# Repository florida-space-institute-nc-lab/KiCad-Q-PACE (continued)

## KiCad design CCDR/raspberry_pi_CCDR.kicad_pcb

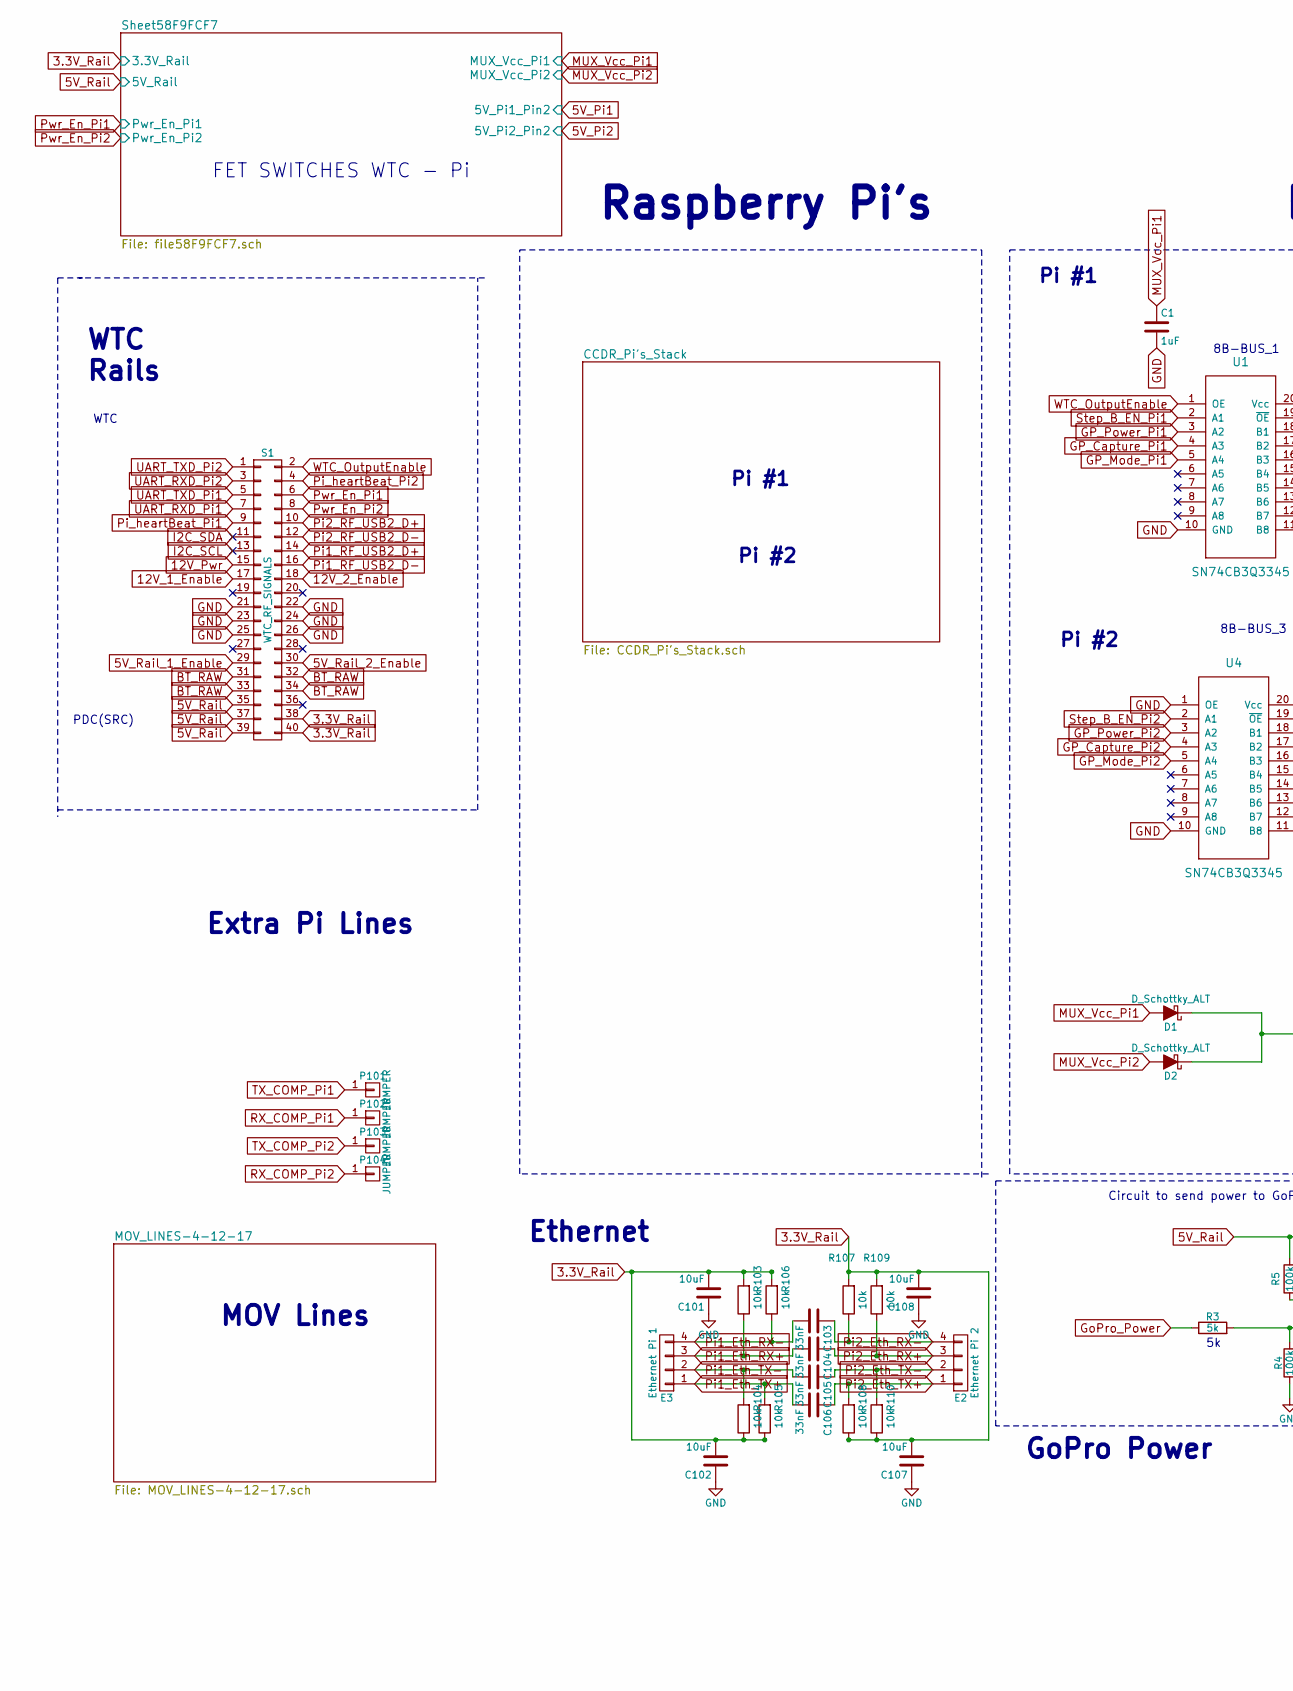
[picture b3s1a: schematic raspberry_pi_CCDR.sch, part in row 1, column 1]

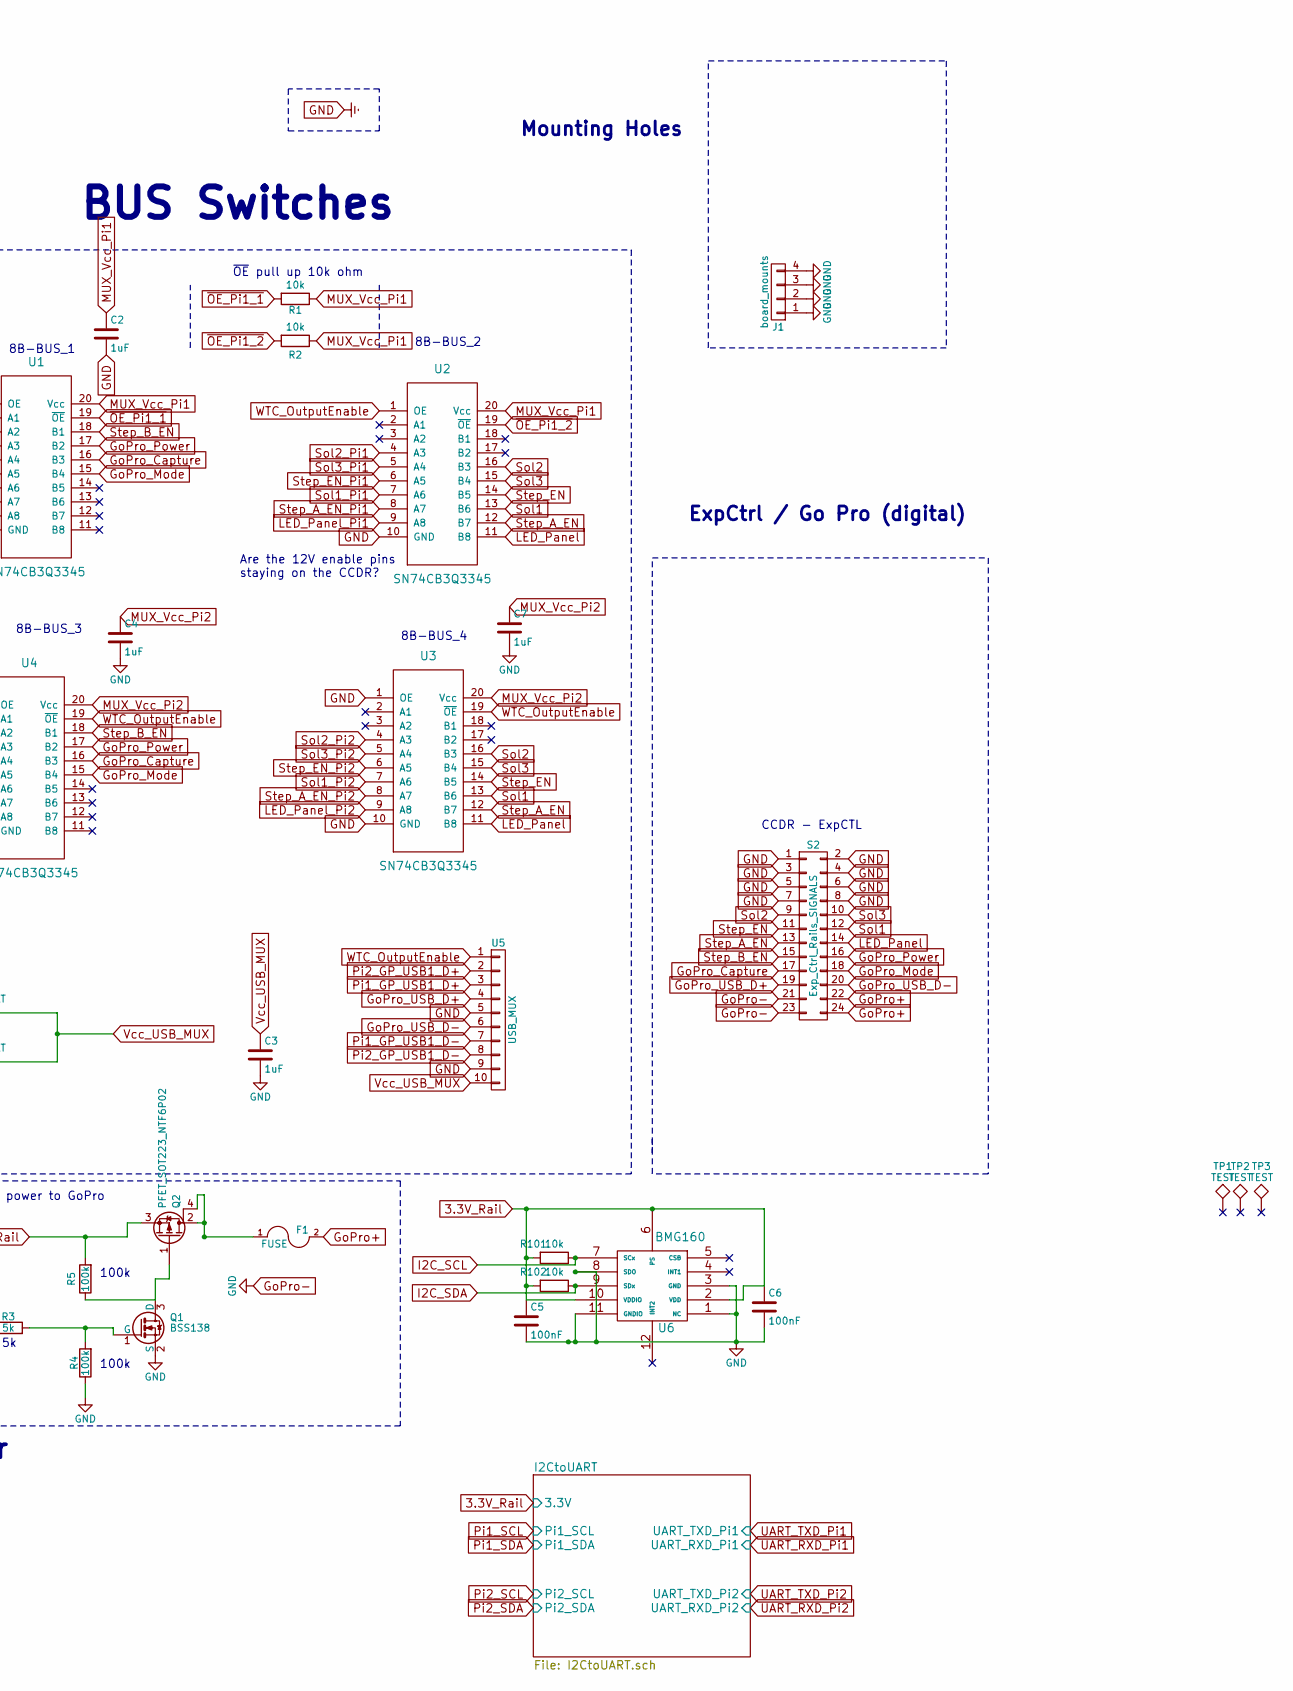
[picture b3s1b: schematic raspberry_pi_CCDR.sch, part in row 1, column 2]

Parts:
C1, C2, C3, C4, C7: 1uF; C_0805_HandSoldering
C5, C6: 100nF; C_0805
C101, C102, C107, C108: 10uF; C_0805
C103, C104, C105, C106: 33nF; C_0805
D1, D2: D_Schottky_ALT; SOD-128
E2: Ethernet Pi 2; 01x04-conn-sq
E3: Ethernet Pi 1; 01x04-conn-sq
F1: FUSE; 2-SMD_Fuse
J1: board_mounts; boardMount_0125in060
P101, P102, P103, P104: JUMPER; PINTST
Q1: BSS138; N-Fet_BSS138_SOT-23
Q2: PFET_SOT223_NTF6P02; SOT-223_GDS
R1, R2, R101, R102, R103, R104, R105, R106, R107, R108, R109, R110: 10k; R_0805
R3: 5k; R_0805
R4, R5: 100k; R_0805
S1: WTC_RF_SIGNALS; Samtec_SSQ-120-03-G-D_QPACE_40-Pin_r1
S2: Exp_Ctrl_Rails_SIGNALS; Samtec_SSQ-112-03-G-D
TP1, TP2, TP3: TEST; Fiducial_0.5mm_Dia_1mm_Outer_FB
U1, U2, U3, U4: SN74CB3Q3345; bus_switch_sn74cb3q3345_rev2
U5: USB_MUX; USB_MUX-TS3USB30E-DGS
U6: BMG160; LGA-12_2x2mm_Pitch0.5mm

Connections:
3.3V_Rail: C5.1, C6.1, C101.2, C102.2, C107.2, C108.2, R101.2, R102.2, R103.2, R104.1, R105.1, R106.2, R107.2, R108.1, R109.2, R110.1, S1.38, S1.40, U6.2 (VDD), U6.6 (PS), U6.10 (VDDIO); also elsewhere on the board
5V_Rail: Q2.3 (S), R5.2, S1.35, S1.37, S1.39; also elsewhere on the board
5V_Rail_1_Enable: S1.29
5V_Rail_2_Enable: S1.30
12V_1_Enable: S1.17
12V_2_Enable: S1.18
12V_Pwr: S1.15
BT_RAW: S1.31, S1.32, S1.33, S1.34
GND: C1.2, C2.2, C3.2, C4.2, C5.2, C6.2, C7.2, C101.1, C102.1, C107.1, C108.1, J1.1, J1.2, J1.3, J1.4, Q1.2 (S), R4.1, S1.21, S1.22, S1.23, S1.24, S1.25, S1.26, S2.1, S2.2, S2.3, S2.4, S2.5, S2.6, S2.7, S2.8, S2.21, S2.23, U1.10 (GND), U2.10 (GND), U3.1 (OE), U3.10 (GND), U4.1 (OE), U4.10 (GND), U5.5, U5.9, U6.1 (NC), U6.3 (GND), U6.8 (SDO), U6.11 (GNDIO); also elsewhere on the board
GP_Capture_Pi1: U1.4 (A3); also elsewhere on the board
GP_Capture_Pi2: U4.4 (A3); also elsewhere on the board
GP_Mode_Pi1: U1.5 (A4); also elsewhere on the board
GP_Mode_Pi2: U4.5 (A4); also elsewhere on the board
GP_Power_Pi1: U1.3 (A2); also elsewhere on the board
GP_Power_Pi2: U4.3 (A2); also elsewhere on the board
GoPro+: F1.2, S2.22, S2.24
GoPro_Capture: S2.17, U1.16 (B3), U4.16 (B3)
GoPro_Mode: S2.18, U1.15 (B4), U4.15 (B4)
GoPro_Power: R3.1, S2.16, U1.17 (B2), U4.17 (B2)
GoPro_USB_D+: S2.19, U5.4
GoPro_USB_D-: S2.20, U5.6
I2C_SCL: R101.1, S1.13, U6.7 (SCx)
I2C_SDA: R102.1, S1.11, U6.9 (SDx)
LED_Panel: S2.14, U2.11 (B8), U3.11 (B8)
LED_Panel_Pi1: U2.9 (A8); also elsewhere on the board
LED_Panel_Pi2: U3.9 (A8); also elsewhere on the board
MUX_Vcc_Pi1: C1.1, C2.1, D1.2 (A), R1.1, R2.1, U1.20 (Vcc), U2.20 (Vcc); also elsewhere on the board
MUX_Vcc_Pi2: C4.1, C7.1, D2.2 (A), U3.20 (Vcc), U4.20 (Vcc); also elsewhere on the board
unnamed: F1.1, Q2.2 (D), Q2.4 (D)
unnamed: Q1.1 (G), R3.2, R4.2
unnamed: Q1.3 (D), Q2.1 (G), R5.1
Pi1_Eth_RX+: C104.2, E3.3, R103.1
Pi1_Eth_RX-: C103.2, E3.4, R106.1
Pi1_Eth_TX+: C106.2, E3.1, R105.2
Pi1_Eth_TX-: C105.2, E3.2, R104.2
Pi1_GP_USB1_D+: U5.3; also elsewhere on the board
Pi1_GP_USB1_D-: U5.7; also elsewhere on the board
Pi1_RF_USB2_D+: S1.14; also elsewhere on the board
Pi1_RF_USB2_D-: S1.16; also elsewhere on the board
Pi2_Eth_RX+: C104.1, E2.3, R109.1
Pi2_Eth_RX-: C103.1, E2.4, R107.1
Pi2_Eth_TX+: C106.1, E2.1, R108.2
Pi2_Eth_TX-: C105.1, E2.2, R110.2
Pi2_GP_USB1_D+: U5.2; also elsewhere on the board
Pi2_GP_USB1_D-: U5.8; also elsewhere on the board
Pi2_RF_USB2_D+: S1.10; also elsewhere on the board
Pi2_RF_USB2_D-: S1.12; also elsewhere on the board
Pi_heartBeat_Pi1: S1.9; also elsewhere on the board
Pi_heartBeat_Pi2: S1.4; also elsewhere on the board
Pwr_En_Pi1: S1.6; also elsewhere on the board
Pwr_En_Pi2: S1.8; also elsewhere on the board
RX_COMP_Pi1: P102.1; also elsewhere on the board
RX_COMP_Pi2: P104.1; also elsewhere on the board
Sol1: S2.12, U2.13 (B6), U3.13 (B6)
Sol1_Pi1: U2.7 (A6); also elsewhere on the board
Sol1_Pi2: U3.7 (A6); also elsewhere on the board
Sol2: S2.9, U2.16 (B3), U3.16 (B3)
Sol2_Pi1: U2.4 (A3); also elsewhere on the board
Sol2_Pi2: U3.4 (A3); also elsewhere on the board
Sol3: S2.10, U2.15 (B4), U3.15 (B4)
Sol3_Pi1: U2.5 (A4); also elsewhere on the board
Sol3_Pi2: U3.5 (A4); also elsewhere on the board
Step_A_EN: S2.13, U2.12 (B7), U3.12 (B7)
Step_A_EN_Pi1: U2.8 (A7); also elsewhere on the board
Step_A_EN_Pi2: U3.8 (A7); also elsewhere on the board
Step_B_EN: S2.15, U1.18 (B1), U4.18 (B1)
Step_B_EN_Pi1: U1.2 (A1); also elsewhere on the board
Step_B_EN_Pi2: U4.2 (A1); also elsewhere on the board
Step_EN: S2.11, U2.14 (B5), U3.14 (B5)
Step_EN_Pi1: U2.6 (A5); also elsewhere on the board
Step_EN_Pi2: U3.6 (A5); also elsewhere on the board
TX_COMP_Pi1: P101.1; also elsewhere on the board
TX_COMP_Pi2: P103.1; also elsewhere on the board
UART_RXD_Pi1: S1.7; also elsewhere on the board
UART_RXD_Pi2: S1.3; also elsewhere on the board
UART_TXD_Pi1: S1.5; also elsewhere on the board
UART_TXD_Pi2: S1.1; also elsewhere on the board
Vcc_USB_MUX: C3.1, D1.1 (K), D2.1 (K), U5.10
WTC_OutputEnable: S1.2, U1.1 (OE), U2.1 (OE), U3.19 (~OE), U4.19 (~OE), U5.1
~OE_Pi1_1: R1.2, U1.19 (~OE)
~OE_Pi1_2: R2.2, U2.19 (~OE)

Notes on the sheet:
PDC(SRC)
8B-BUS_1
8B-BUS_2
8B-BUS_3
8B-BUS_4
CCDR - ExpCTL
Raspberry Pi's
BUS Switches
ExpCtrl / Go Pro (digital)
WTC Rails
GoPro Power
Mounting Holes
Pi #1
Pi #2
WTC
MOV Lines
~OE~ pull up 10k ohm
FET SWITCHES WTC - Pi
Circuit to send power to GoPro
Are the 12V enable pins staying on the CCDR?
100k
Extra Pi Lines
Ethernet

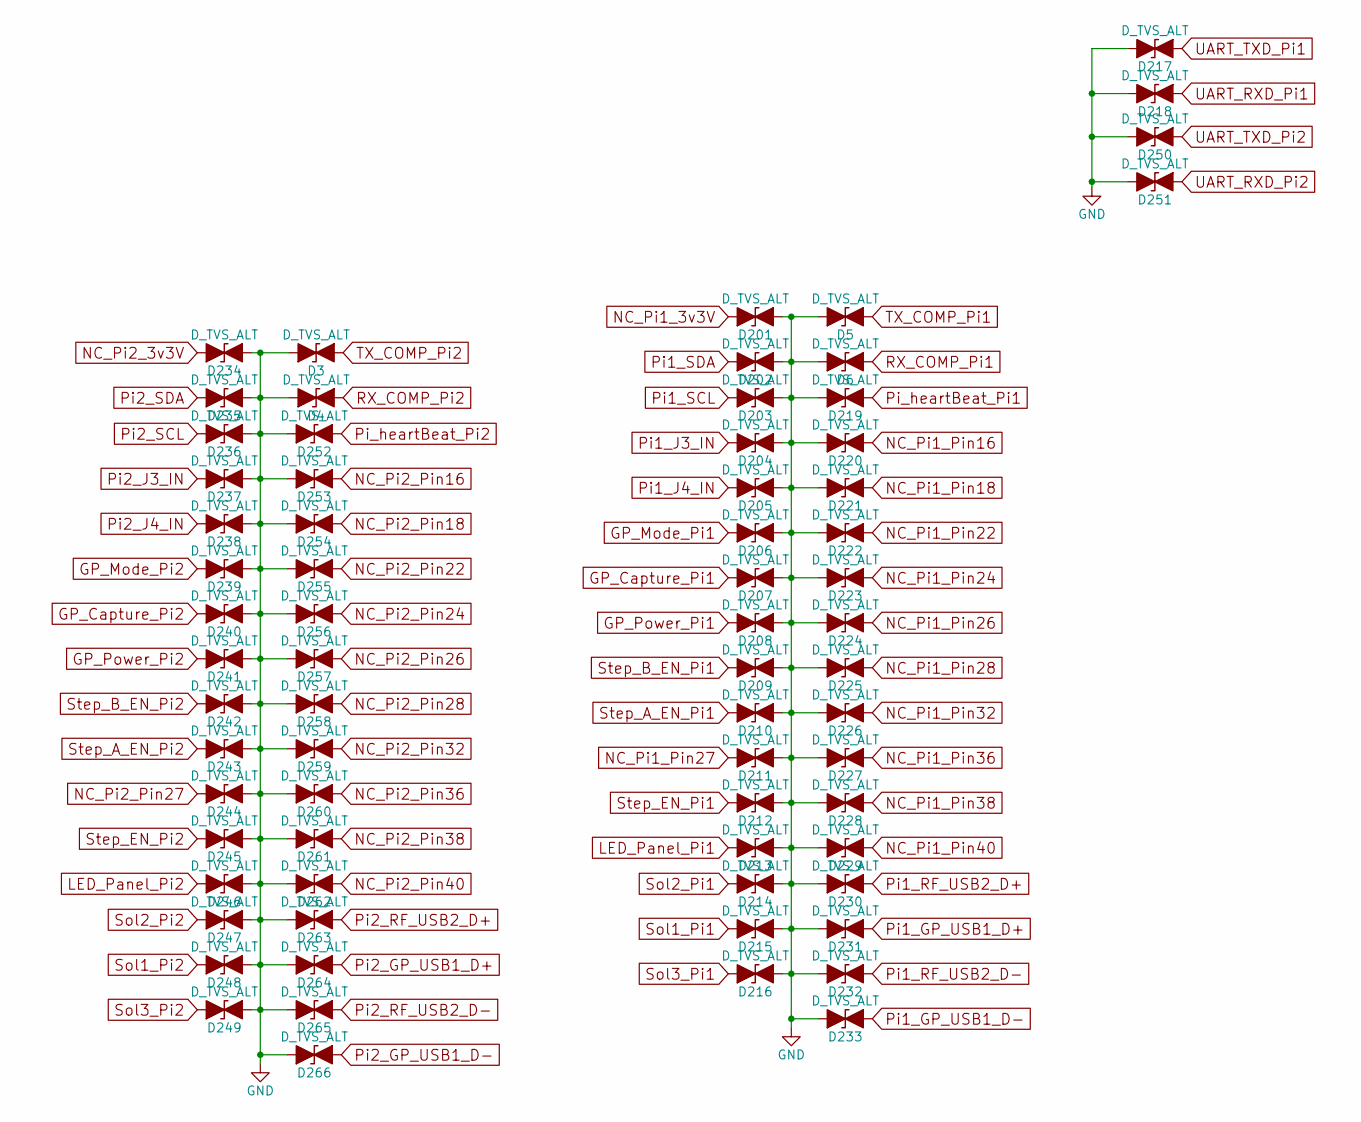
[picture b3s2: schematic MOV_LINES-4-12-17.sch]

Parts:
D3, D4, D5, D6, D201, D202, D203, D204, D205, D206, D207, D208, D209, D210, D211, D212, D213, D214, D215, D216, D217, D218, D219, D220, D221, D222, D223, D224, D225, D226, D227, D228, D229, D230, D231, D232, D233, D234, D235, D236, D237, D238, D239, D240, D241, D242, D243, D244, D245, D246, D247, D248, D249, D250, D251, D252, D253, D254, D255, D256, D257, D258, D259, D260, D261, D262, D263, D264, D265, D266: D_TVS_ALT; D_0805

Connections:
GND: D3.2 (A2), D4.2 (A2), D5.2 (A2), D6.2 (A2), D201.1 (A1), D202.1 (A1), D203.1 (A1), D204.1 (A1), D205.1 (A1), D206.1 (A1), D207.1 (A1), D208.1 (A1), D209.1 (A1), D210.1 (A1), D211.1 (A1), D212.1 (A1), D213.1 (A1), D214.1 (A1), D215.1 (A1), D216.1 (A1), D217.2 (A2), D218.2 (A2), D219.2 (A2), D220.2 (A2), D221.2 (A2), D222.2 (A2), D223.2 (A2), D224.2 (A2), D225.2 (A2), D226.2 (A2), D227.2 (A2), D228.2 (A2), D229.2 (A2), D230.2 (A2), D231.2 (A2), D232.2 (A2), D233.2 (A2), D234.1 (A1), D235.1 (A1), D236.1 (A1), D237.1 (A1), D238.1 (A1), D239.1 (A1), D240.1 (A1), D241.1 (A1), D242.1 (A1), D243.1 (A1), D244.1 (A1), D245.1 (A1), D246.1 (A1), D247.1 (A1), D248.1 (A1), D249.1 (A1), D250.2 (A2), D251.2 (A2), D252.2 (A2), D253.2 (A2), D254.2 (A2), D255.2 (A2), D256.2 (A2), D257.2 (A2), D258.2 (A2), D259.2 (A2), D260.2 (A2), D261.2 (A2), D262.2 (A2), D263.2 (A2), D264.2 (A2), D265.2 (A2), D266.2 (A2); also elsewhere on the board
GP_Capture_Pi1: D207.2 (A2); also elsewhere on the board
GP_Capture_Pi2: D240.2 (A2); also elsewhere on the board
GP_Mode_Pi1: D206.2 (A2); also elsewhere on the board
GP_Mode_Pi2: D239.2 (A2); also elsewhere on the board
GP_Power_Pi1: D208.2 (A2); also elsewhere on the board
GP_Power_Pi2: D241.2 (A2); also elsewhere on the board
LED_Panel_Pi1: D213.2 (A2); also elsewhere on the board
LED_Panel_Pi2: D246.2 (A2); also elsewhere on the board
NC_Pi1_3v3V: D201.2 (A2); also elsewhere on the board
NC_Pi1_Pin16: D220.1 (A1); also elsewhere on the board
NC_Pi1_Pin18: D221.1 (A1); also elsewhere on the board
NC_Pi1_Pin22: D222.1 (A1); also elsewhere on the board
NC_Pi1_Pin24: D223.1 (A1); also elsewhere on the board
NC_Pi1_Pin26: D224.1 (A1); also elsewhere on the board
NC_Pi1_Pin27: D211.2 (A2); also elsewhere on the board
NC_Pi1_Pin28: D225.1 (A1); also elsewhere on the board
NC_Pi1_Pin32: D226.1 (A1); also elsewhere on the board
NC_Pi1_Pin36: D227.1 (A1); also elsewhere on the board
NC_Pi1_Pin38: D228.1 (A1); also elsewhere on the board
NC_Pi1_Pin40: D229.1 (A1); also elsewhere on the board
NC_Pi2_3v3V: D234.2 (A2); also elsewhere on the board
NC_Pi2_Pin16: D253.1 (A1); also elsewhere on the board
NC_Pi2_Pin18: D254.1 (A1); also elsewhere on the board
NC_Pi2_Pin22: D255.1 (A1); also elsewhere on the board
NC_Pi2_Pin24: D256.1 (A1); also elsewhere on the board
NC_Pi2_Pin26: D257.1 (A1); also elsewhere on the board
NC_Pi2_Pin27: D244.2 (A2); also elsewhere on the board
NC_Pi2_Pin28: D258.1 (A1); also elsewhere on the board
NC_Pi2_Pin32: D259.1 (A1); also elsewhere on the board
NC_Pi2_Pin36: D260.1 (A1); also elsewhere on the board
NC_Pi2_Pin38: D261.1 (A1); also elsewhere on the board
NC_Pi2_Pin40: D262.1 (A1); also elsewhere on the board
Pi1_GP_USB1_D+: D231.1 (A1); also elsewhere on the board
Pi1_GP_USB1_D-: D233.1 (A1); also elsewhere on the board
Pi1_J3_IN: D204.2 (A2); also elsewhere on the board
Pi1_J4_IN: D205.2 (A2); also elsewhere on the board
Pi1_RF_USB2_D+: D230.1 (A1); also elsewhere on the board
Pi1_RF_USB2_D-: D232.1 (A1); also elsewhere on the board
Pi1_SCL: D203.2 (A2); also elsewhere on the board
Pi1_SDA: D202.2 (A2); also elsewhere on the board
Pi2_GP_USB1_D+: D264.1 (A1); also elsewhere on the board
Pi2_GP_USB1_D-: D266.1 (A1); also elsewhere on the board
Pi2_J3_IN: D237.2 (A2); also elsewhere on the board
Pi2_J4_IN: D238.2 (A2); also elsewhere on the board
Pi2_RF_USB2_D+: D263.1 (A1); also elsewhere on the board
Pi2_RF_USB2_D-: D265.1 (A1); also elsewhere on the board
Pi2_SCL: D236.2 (A2); also elsewhere on the board
Pi2_SDA: D235.2 (A2); also elsewhere on the board
Pi_heartBeat_Pi1: D219.1 (A1); also elsewhere on the board
Pi_heartBeat_Pi2: D252.1 (A1); also elsewhere on the board
RX_COMP_Pi1: D6.1 (A1); also elsewhere on the board
RX_COMP_Pi2: D4.1 (A1); also elsewhere on the board
Sol1_Pi1: D215.2 (A2); also elsewhere on the board
Sol1_Pi2: D248.2 (A2); also elsewhere on the board
Sol2_Pi1: D214.2 (A2); also elsewhere on the board
Sol2_Pi2: D247.2 (A2); also elsewhere on the board
Sol3_Pi1: D216.2 (A2); also elsewhere on the board
Sol3_Pi2: D249.2 (A2); also elsewhere on the board
Step_A_EN_Pi1: D210.2 (A2); also elsewhere on the board
Step_A_EN_Pi2: D243.2 (A2); also elsewhere on the board
Step_B_EN_Pi1: D209.2 (A2); also elsewhere on the board
Step_B_EN_Pi2: D242.2 (A2); also elsewhere on the board
Step_EN_Pi1: D212.2 (A2); also elsewhere on the board
Step_EN_Pi2: D245.2 (A2); also elsewhere on the board
TX_COMP_Pi1: D5.1 (A1); also elsewhere on the board
TX_COMP_Pi2: D3.1 (A1); also elsewhere on the board
UART_RXD_Pi1: D218.1 (A1); also elsewhere on the board
UART_RXD_Pi2: D251.1 (A1); also elsewhere on the board
UART_TXD_Pi1: D217.1 (A1); also elsewhere on the board
UART_TXD_Pi2: D250.1 (A1); also elsewhere on the board

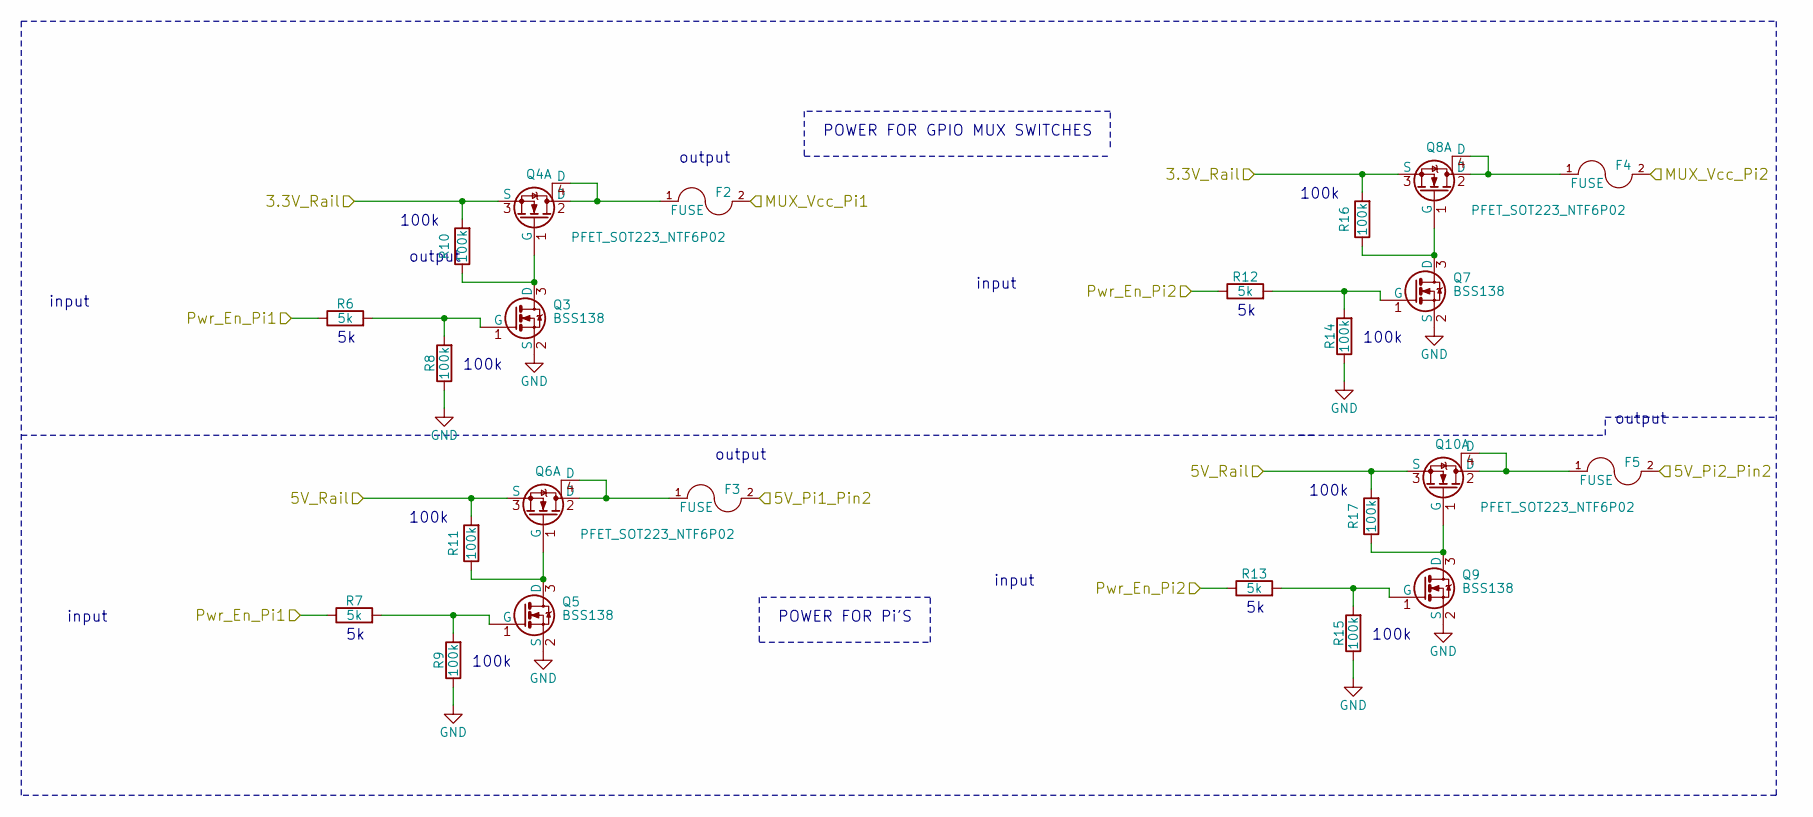
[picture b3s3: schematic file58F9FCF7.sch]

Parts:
F2, F3, F4, F5: FUSE; 2-SMD_Fuse
Q3, Q5, Q7, Q9: BSS138; N-Fet_BSS138_SOT-23
Q4, Q6, Q8, Q10: PFET_SOT223_NTF6P02; SOT-223_GDS
R6, R7, R12, R13: 5k; R_0805
R8, R9, R10, R11, R14, R15, R16, R17: 100k; R_0805

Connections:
3.3V_Rail: Q4.3 (S), Q8.3 (S), R10.2, R16.2; also elsewhere on the board
5V_Pi1: F3.2; also elsewhere on the board
5V_Pi2: F5.2; also elsewhere on the board
5V_Rail: Q6.3 (S), Q10.3 (S), R11.2, R17.2; also elsewhere on the board
GND: Q3.2 (S), Q5.2 (S), Q7.2 (S), Q9.2 (S), R8.1, R9.1, R14.1, R15.1; also elsewhere on the board
MUX_Vcc_Pi1: F2.2; also elsewhere on the board
MUX_Vcc_Pi2: F4.2; also elsewhere on the board
unnamed: F2.1, Q4.2 (D), Q4.4 (D)
unnamed: F3.1, Q6.2 (D), Q6.4 (D)
unnamed: F4.1, Q8.2 (D), Q8.4 (D)
unnamed: F5.1, Q10.2 (D), Q10.4 (D)
unnamed: Q3.1 (G), R6.2, R8.2
unnamed: Q3.3 (D), Q4.1 (G), R10.1
unnamed: Q5.1 (G), R7.2, R9.2
unnamed: Q5.3 (D), Q6.1 (G), R11.1
unnamed: Q7.1 (G), R12.2, R14.2
unnamed: Q7.3 (D), Q8.1 (G), R16.1
unnamed: Q9.1 (G), R13.2, R15.2
unnamed: Q9.3 (D), Q10.1 (G), R17.1
Pwr_En_Pi1: R6.1, R7.1; also elsewhere on the board
Pwr_En_Pi2: R12.1, R13.1; also elsewhere on the board

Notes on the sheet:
100k
input
output
POWER FOR GPIO MUX SWITCHES
POWER FOR Pi'S

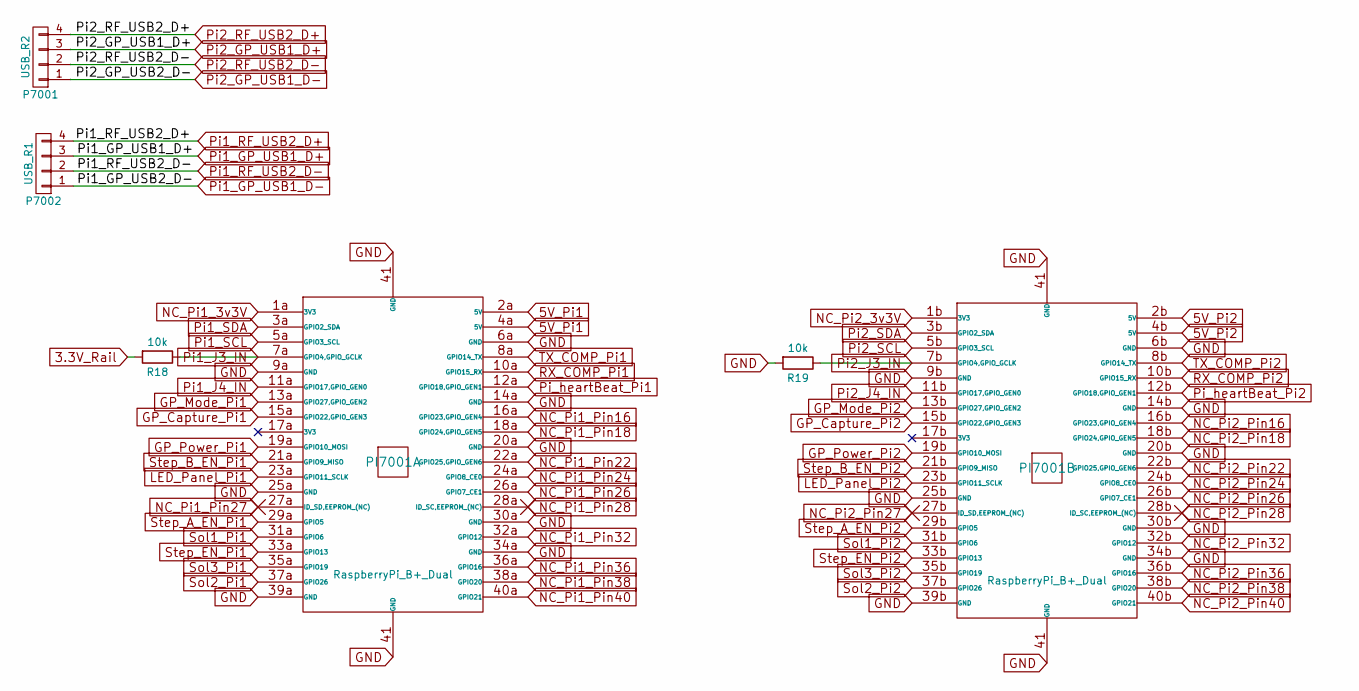
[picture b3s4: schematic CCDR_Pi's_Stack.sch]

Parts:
P7001: USB_R2; USB_2.0_2_port_4conn
P7002: USB_R1; USB_2.0_2_port_4conn
PI7001: RaspberryPi_B+_Dual; 2x40_socket_966240-2000_FLIPPED
R18, R19: 10k; R_0805

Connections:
3.3V_Rail: R18.2; also elsewhere on the board
5V_Pi1: PI7001.2a (5V), PI7001.4a (5V); also elsewhere on the board
5V_Pi2: PI7001.2b (5V), PI7001.4b (5V); also elsewhere on the board
GND: PI7001.6a (GND), PI7001.6b (GND), PI7001.9a (GND), PI7001.9b (GND), PI7001.14a (GND), PI7001.14b (GND), PI7001.20a (GND), PI7001.20b (GND), PI7001.25a (GND), PI7001.25b (GND), PI7001.30a (GND), PI7001.30b (GND), PI7001.34a (GND), PI7001.34b (GND), PI7001.39a (GND), PI7001.39b (GND), PI7001.41 (GND), R19.2; also elsewhere on the board
GP_Capture_Pi1: PI7001.15a (GPIO22,GPIO_GEN3); also elsewhere on the board
GP_Capture_Pi2: PI7001.15b (GPIO22,GPIO_GEN3); also elsewhere on the board
GP_Mode_Pi1: PI7001.13a (GPIO27,GPIO_GEN2); also elsewhere on the board
GP_Mode_Pi2: PI7001.13b (GPIO27,GPIO_GEN2); also elsewhere on the board
GP_Power_Pi1: PI7001.19a (GPIO10_MOSI); also elsewhere on the board
GP_Power_Pi2: PI7001.19b (GPIO10_MOSI); also elsewhere on the board
LED_Panel_Pi1: PI7001.23a (GPIO11_SCLK); also elsewhere on the board
LED_Panel_Pi2: PI7001.23b (GPIO11_SCLK); also elsewhere on the board
NC_Pi1_3v3V: PI7001.1a (3V3); also elsewhere on the board
NC_Pi1_Pin16: PI7001.16a (GPIO23,GPIO_GEN4); also elsewhere on the board
NC_Pi1_Pin18: PI7001.18a (GPIO24,GPIO_GEN5); also elsewhere on the board
NC_Pi1_Pin22: PI7001.22a (GPIO25,GPIO_GEN6); also elsewhere on the board
NC_Pi1_Pin24: PI7001.24a (GPIO8_CE0); also elsewhere on the board
NC_Pi1_Pin26: PI7001.26a (GPIO7_CE1); also elsewhere on the board
NC_Pi1_Pin27: PI7001.27a (ID_SD,EEPROM_(NC)); also elsewhere on the board
NC_Pi1_Pin28: PI7001.28a (ID_SC,EEPROM_(NC)); also elsewhere on the board
NC_Pi1_Pin32: PI7001.32a (GPIO12); also elsewhere on the board
NC_Pi1_Pin36: PI7001.36a (GPIO16); also elsewhere on the board
NC_Pi1_Pin38: PI7001.38a (GPIO20); also elsewhere on the board
NC_Pi1_Pin40: PI7001.40a (GPIO21); also elsewhere on the board
NC_Pi2_3v3V: PI7001.1b (3V3); also elsewhere on the board
NC_Pi2_Pin16: PI7001.16b (GPIO23,GPIO_GEN4); also elsewhere on the board
NC_Pi2_Pin18: PI7001.18b (GPIO24,GPIO_GEN5); also elsewhere on the board
NC_Pi2_Pin22: PI7001.22b (GPIO25,GPIO_GEN6); also elsewhere on the board
NC_Pi2_Pin24: PI7001.24b (GPIO8_CE0); also elsewhere on the board
NC_Pi2_Pin26: PI7001.26b (GPIO7_CE1); also elsewhere on the board
NC_Pi2_Pin27: PI7001.27b (ID_SD,EEPROM_(NC)); also elsewhere on the board
NC_Pi2_Pin28: PI7001.28b (ID_SC,EEPROM_(NC)); also elsewhere on the board
NC_Pi2_Pin32: PI7001.32b (GPIO12); also elsewhere on the board
NC_Pi2_Pin36: PI7001.36b (GPIO16); also elsewhere on the board
NC_Pi2_Pin38: PI7001.38b (GPIO20); also elsewhere on the board
NC_Pi2_Pin40: PI7001.40b (GPIO21); also elsewhere on the board
Pi1_GP_USB1_D+: P7002.3; also elsewhere on the board
Pi1_GP_USB1_D-: P7002.1; also elsewhere on the board
Pi1_J3_IN: PI7001.7a (GPIO4,GPIO_GCLK), R18.1; also elsewhere on the board
Pi1_J4_IN: PI7001.11a (GPIO17,GPIO_GEN0); also elsewhere on the board
Pi1_RF_USB2_D+: P7002.4; also elsewhere on the board
Pi1_RF_USB2_D-: P7002.2; also elsewhere on the board
Pi1_SCL: PI7001.5a (GPIO3_SCL); also elsewhere on the board
Pi1_SDA: PI7001.3a (GPIO2_SDA); also elsewhere on the board
Pi2_GP_USB1_D+: P7001.3; also elsewhere on the board
Pi2_GP_USB1_D-: P7001.1; also elsewhere on the board
Pi2_J3_IN: PI7001.7b (GPIO4,GPIO_GCLK), R19.1; also elsewhere on the board
Pi2_J4_IN: PI7001.11b (GPIO17,GPIO_GEN0); also elsewhere on the board
Pi2_RF_USB2_D+: P7001.4; also elsewhere on the board
Pi2_RF_USB2_D-: P7001.2; also elsewhere on the board
Pi2_SCL: PI7001.5b (GPIO3_SCL); also elsewhere on the board
Pi2_SDA: PI7001.3b (GPIO2_SDA); also elsewhere on the board
Pi_heartBeat_Pi1: PI7001.12a (GPIO18,GPIO_GEN1); also elsewhere on the board
Pi_heartBeat_Pi2: PI7001.12b (GPIO18,GPIO_GEN1); also elsewhere on the board
RX_COMP_Pi1: PI7001.10a (GPIO15_RX); also elsewhere on the board
RX_COMP_Pi2: PI7001.10b (GPIO15_RX); also elsewhere on the board
Sol1_Pi1: PI7001.31a (GPIO6); also elsewhere on the board
Sol1_Pi2: PI7001.31b (GPIO6); also elsewhere on the board
Sol2_Pi1: PI7001.37a (GPIO26); also elsewhere on the board
Sol2_Pi2: PI7001.37b (GPIO26); also elsewhere on the board
Sol3_Pi1: PI7001.35a (GPIO19); also elsewhere on the board
Sol3_Pi2: PI7001.35b (GPIO19); also elsewhere on the board
Step_A_EN_Pi1: PI7001.29a (GPIO5); also elsewhere on the board
Step_A_EN_Pi2: PI7001.29b (GPIO5); also elsewhere on the board
Step_B_EN_Pi1: PI7001.21a (GPIO9_MISO); also elsewhere on the board
Step_B_EN_Pi2: PI7001.21b (GPIO9_MISO); also elsewhere on the board
Step_EN_Pi1: PI7001.33a (GPIO13); also elsewhere on the board
Step_EN_Pi2: PI7001.33b (GPIO13); also elsewhere on the board
TX_COMP_Pi1: PI7001.8a (GPIO14_TX); also elsewhere on the board
TX_COMP_Pi2: PI7001.8b (GPIO14_TX); also elsewhere on the board

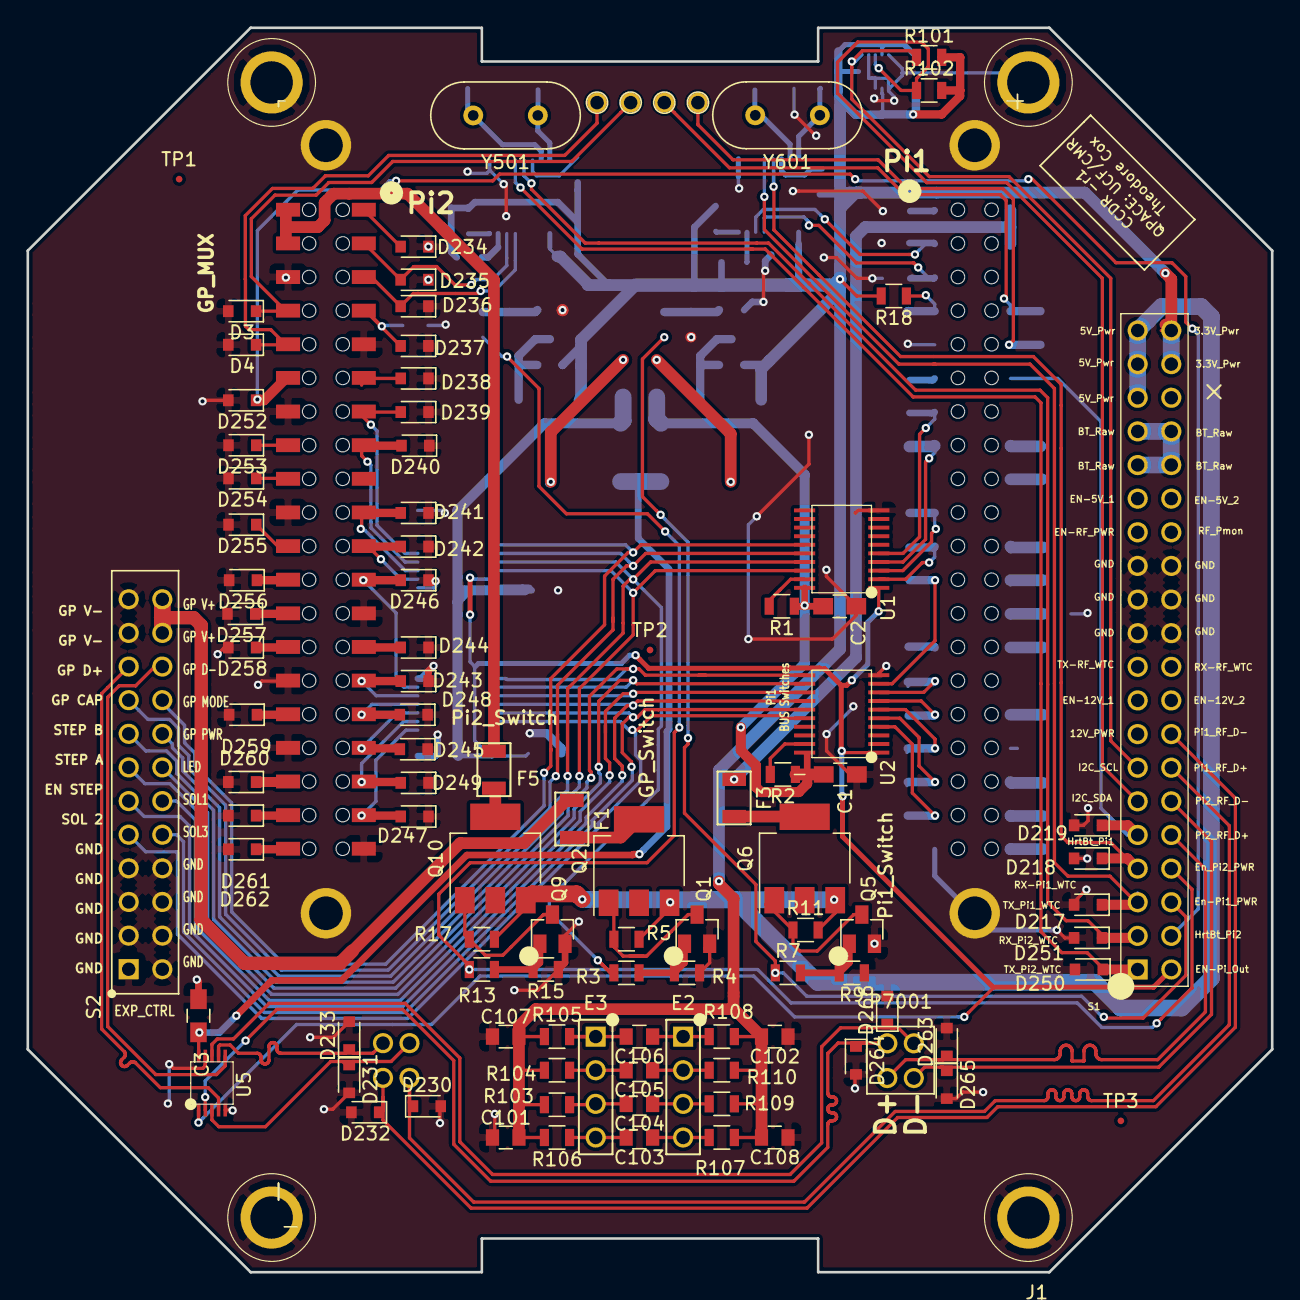
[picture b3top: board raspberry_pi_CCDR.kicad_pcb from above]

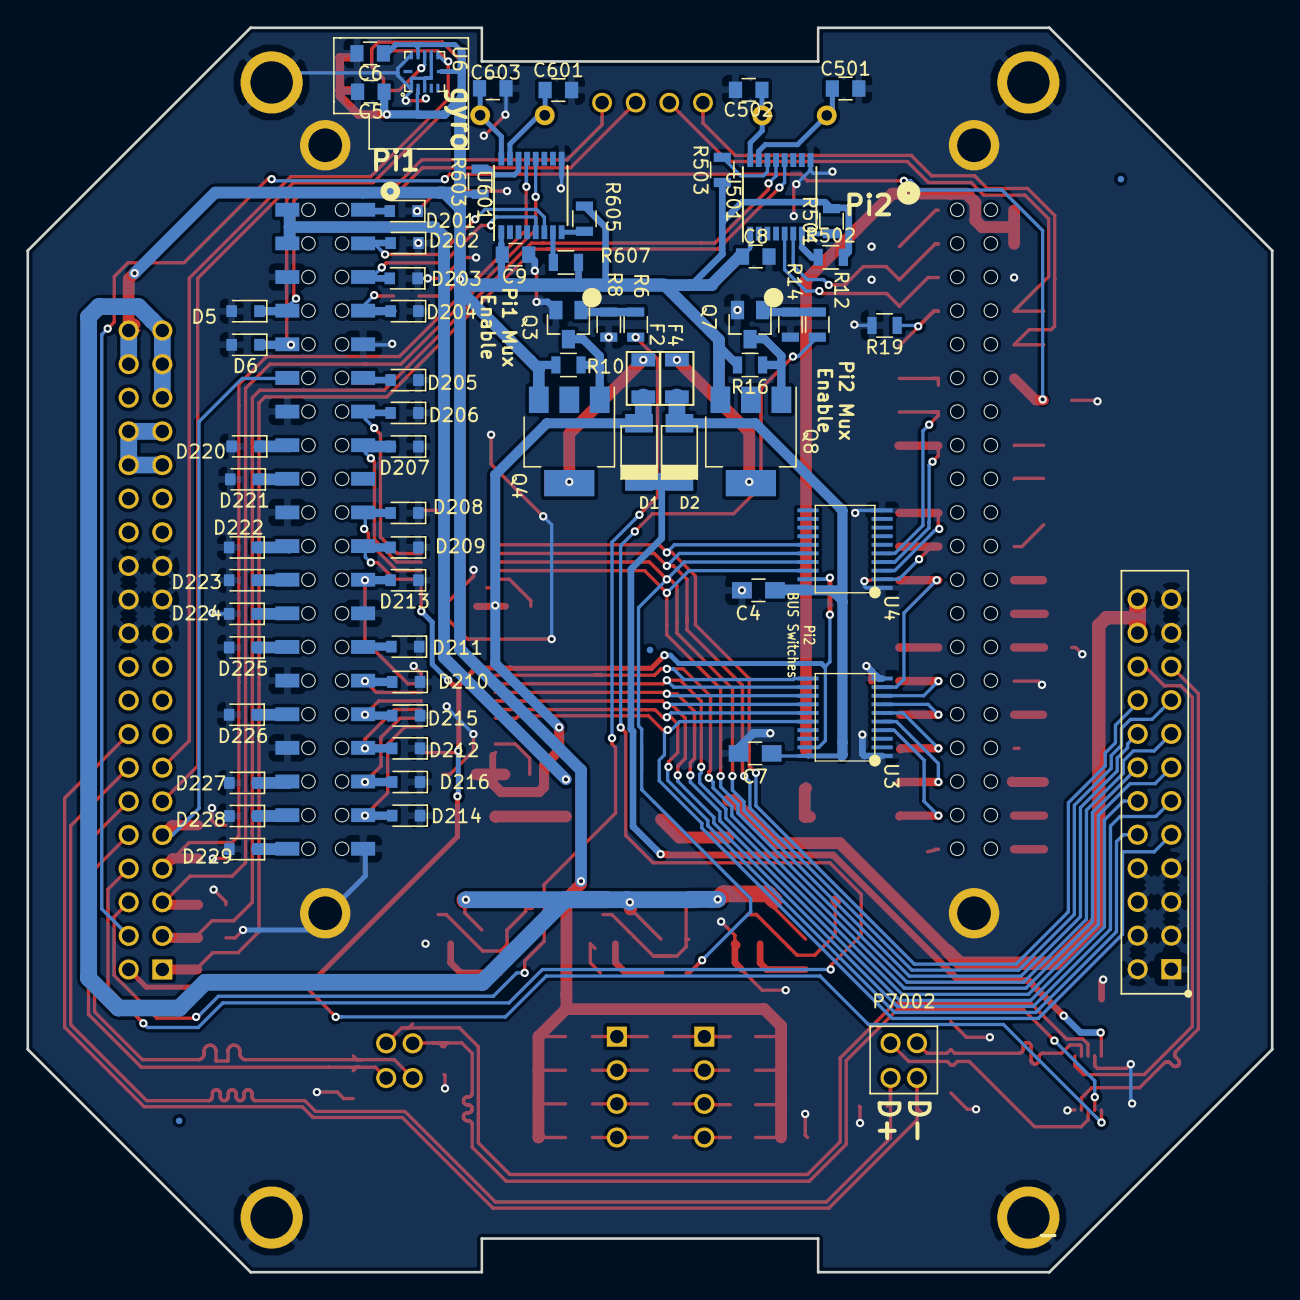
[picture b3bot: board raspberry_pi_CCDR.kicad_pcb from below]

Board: 2 copper layers, 94.0 x 94.0 mm, 168 parts (66 on the bottom side), 132 nets.

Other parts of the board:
C8, C9: 0.1uF; C_0805
C501, C502, C601, C603: 18pF; C_0805
R501, R503, R603, R605: 10k; R_0805
R502, R607: 1k; R_0805
U501, U601: SC16IS750; TSSOP-16-1EP_4.4x5mm_Pitch0.65mm
Y501, Y601: 1.8432MHz; Crystal_HC49-U_Vertical

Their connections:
3.3V_Rail: C8.1, C9.1, R501.2, R502.2, R503.1, R603.1, R605.2, R607.2, U501.1, U601.1; also elsewhere on the board
GND: C8.2, C9.2, C501.2, C502.2, C601.2, C603.2, U501.9, U601.9; also elsewhere on the board
unnamed: C501.1, U501.15, Y501.2
unnamed: C502.1, U501.16, Y501.1
unnamed: C601.1, U601.15, Y601.2
unnamed: C603.1, U601.16, Y601.1
unnamed: R501.1, U501.8
unnamed: R502.1, U501.7
unnamed: R503.2, U501.14
unnamed: R603.2, U601.14
unnamed: R605.1, U601.8
unnamed: R607.1, U601.7
Pi1_SCL: U601.5; also elsewhere on the board
Pi1_SDA: U601.6; also elsewhere on the board
Pi2_SCL: U501.5; also elsewhere on the board
Pi2_SDA: U501.6; also elsewhere on the board
UART_RXD_Pi1: U601.13; also elsewhere on the board
UART_RXD_Pi2: U501.13; also elsewhere on the board
UART_TXD_Pi1: U601.12; also elsewhere on the board
UART_TXD_Pi2: U501.12; also elsewhere on the board
